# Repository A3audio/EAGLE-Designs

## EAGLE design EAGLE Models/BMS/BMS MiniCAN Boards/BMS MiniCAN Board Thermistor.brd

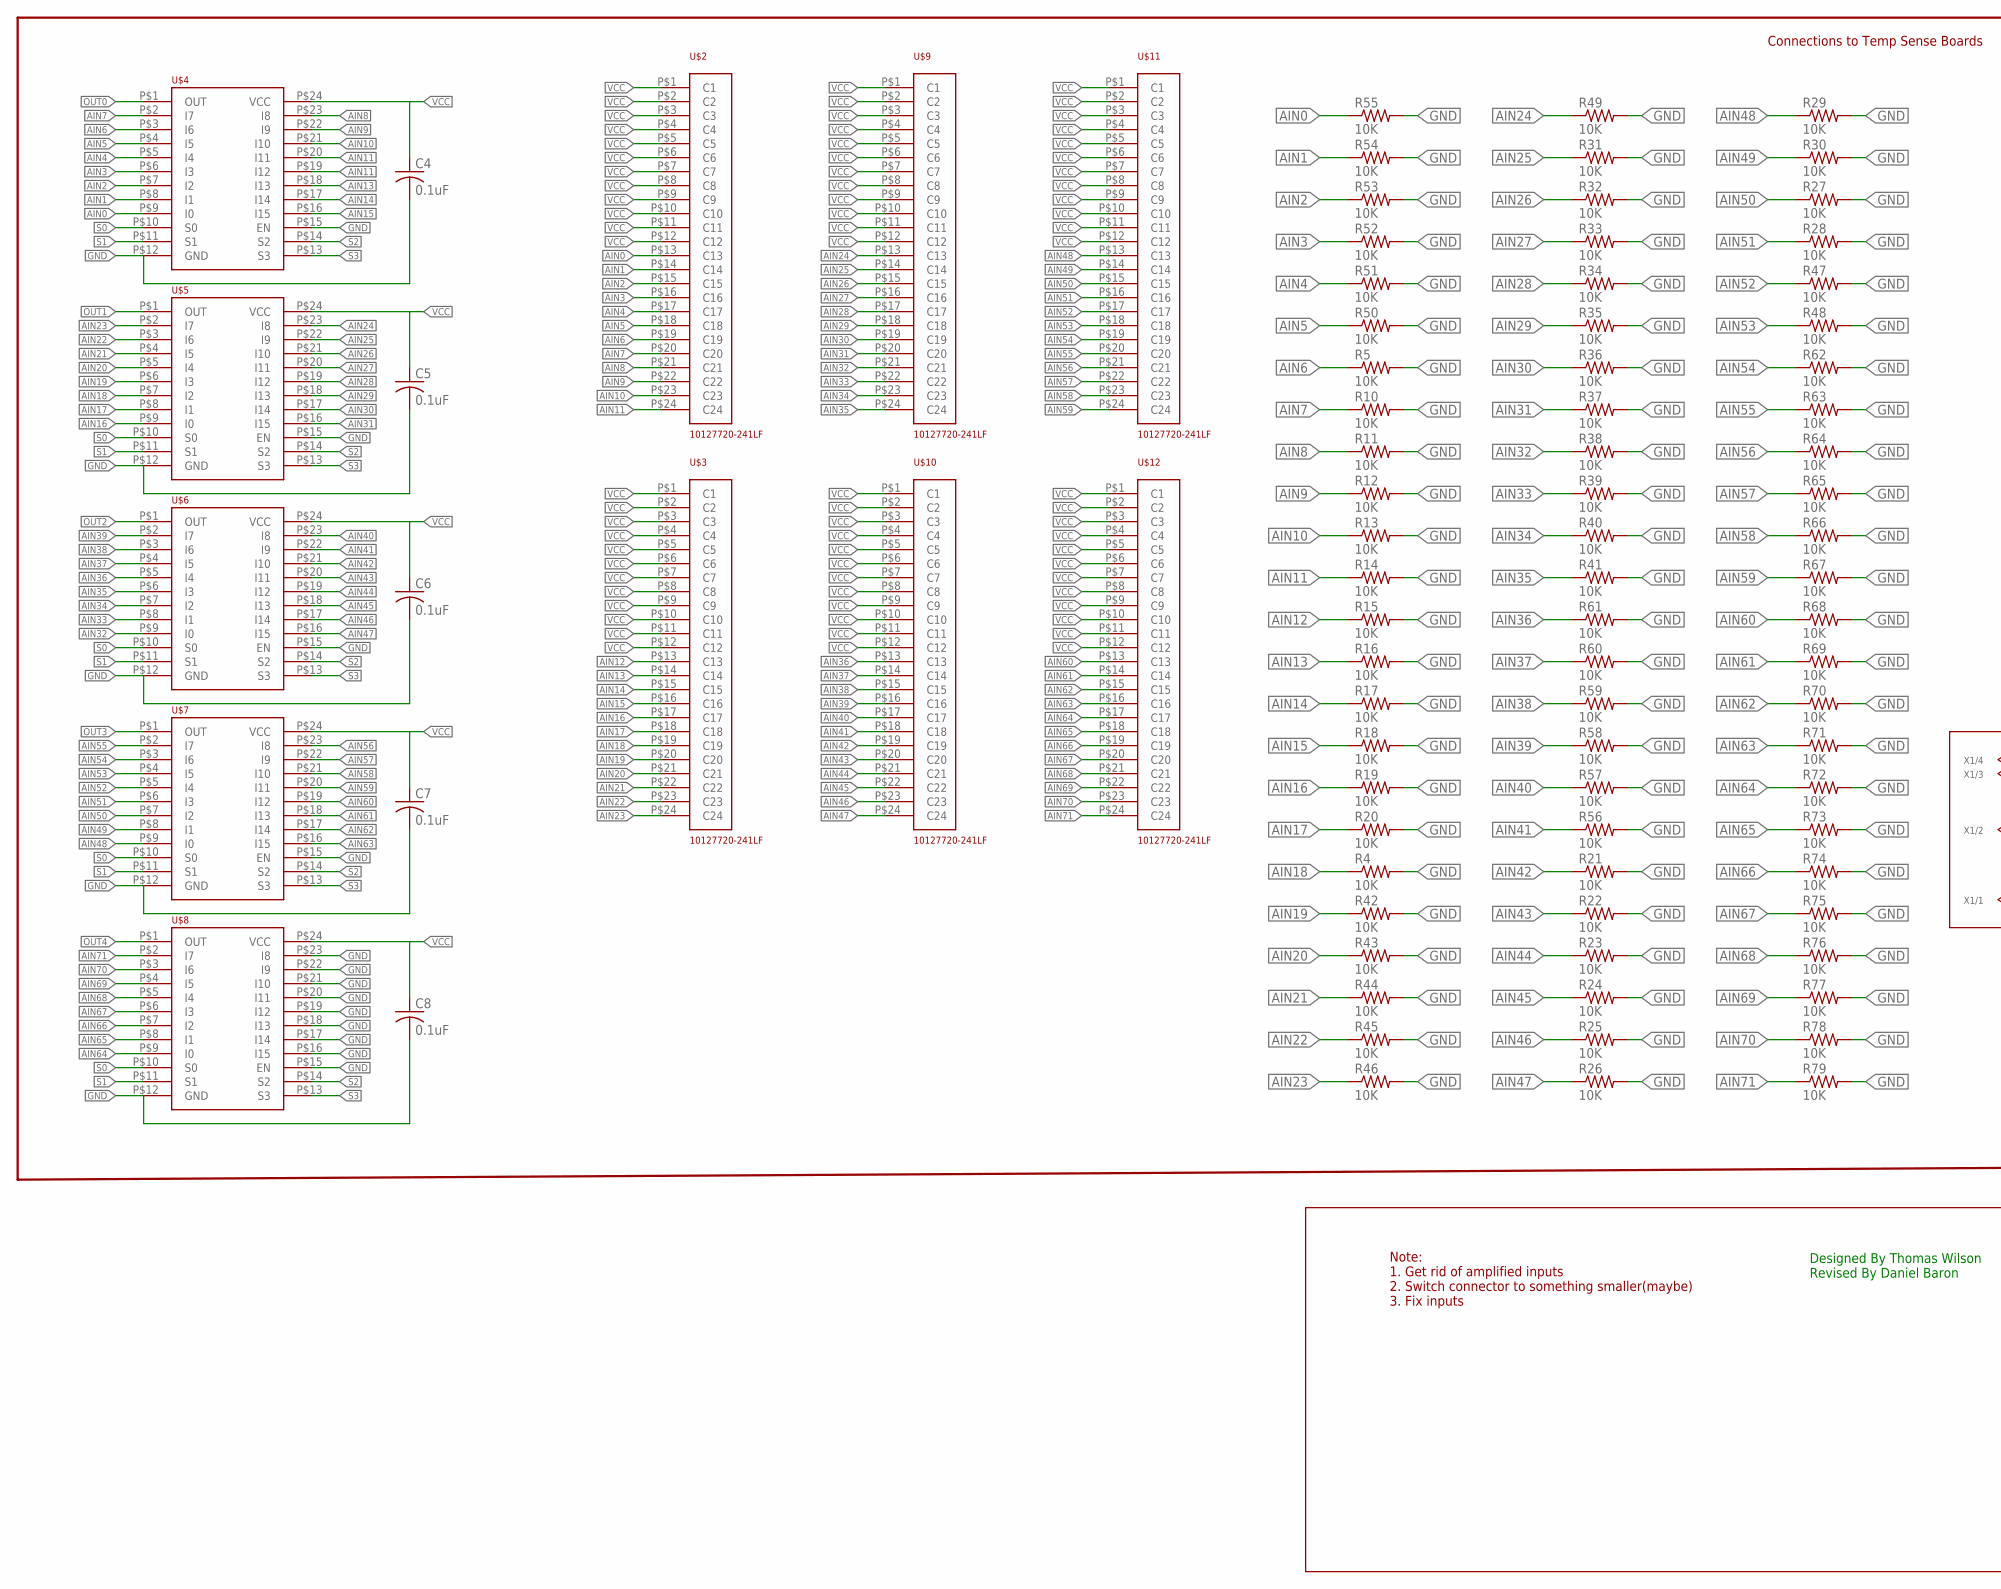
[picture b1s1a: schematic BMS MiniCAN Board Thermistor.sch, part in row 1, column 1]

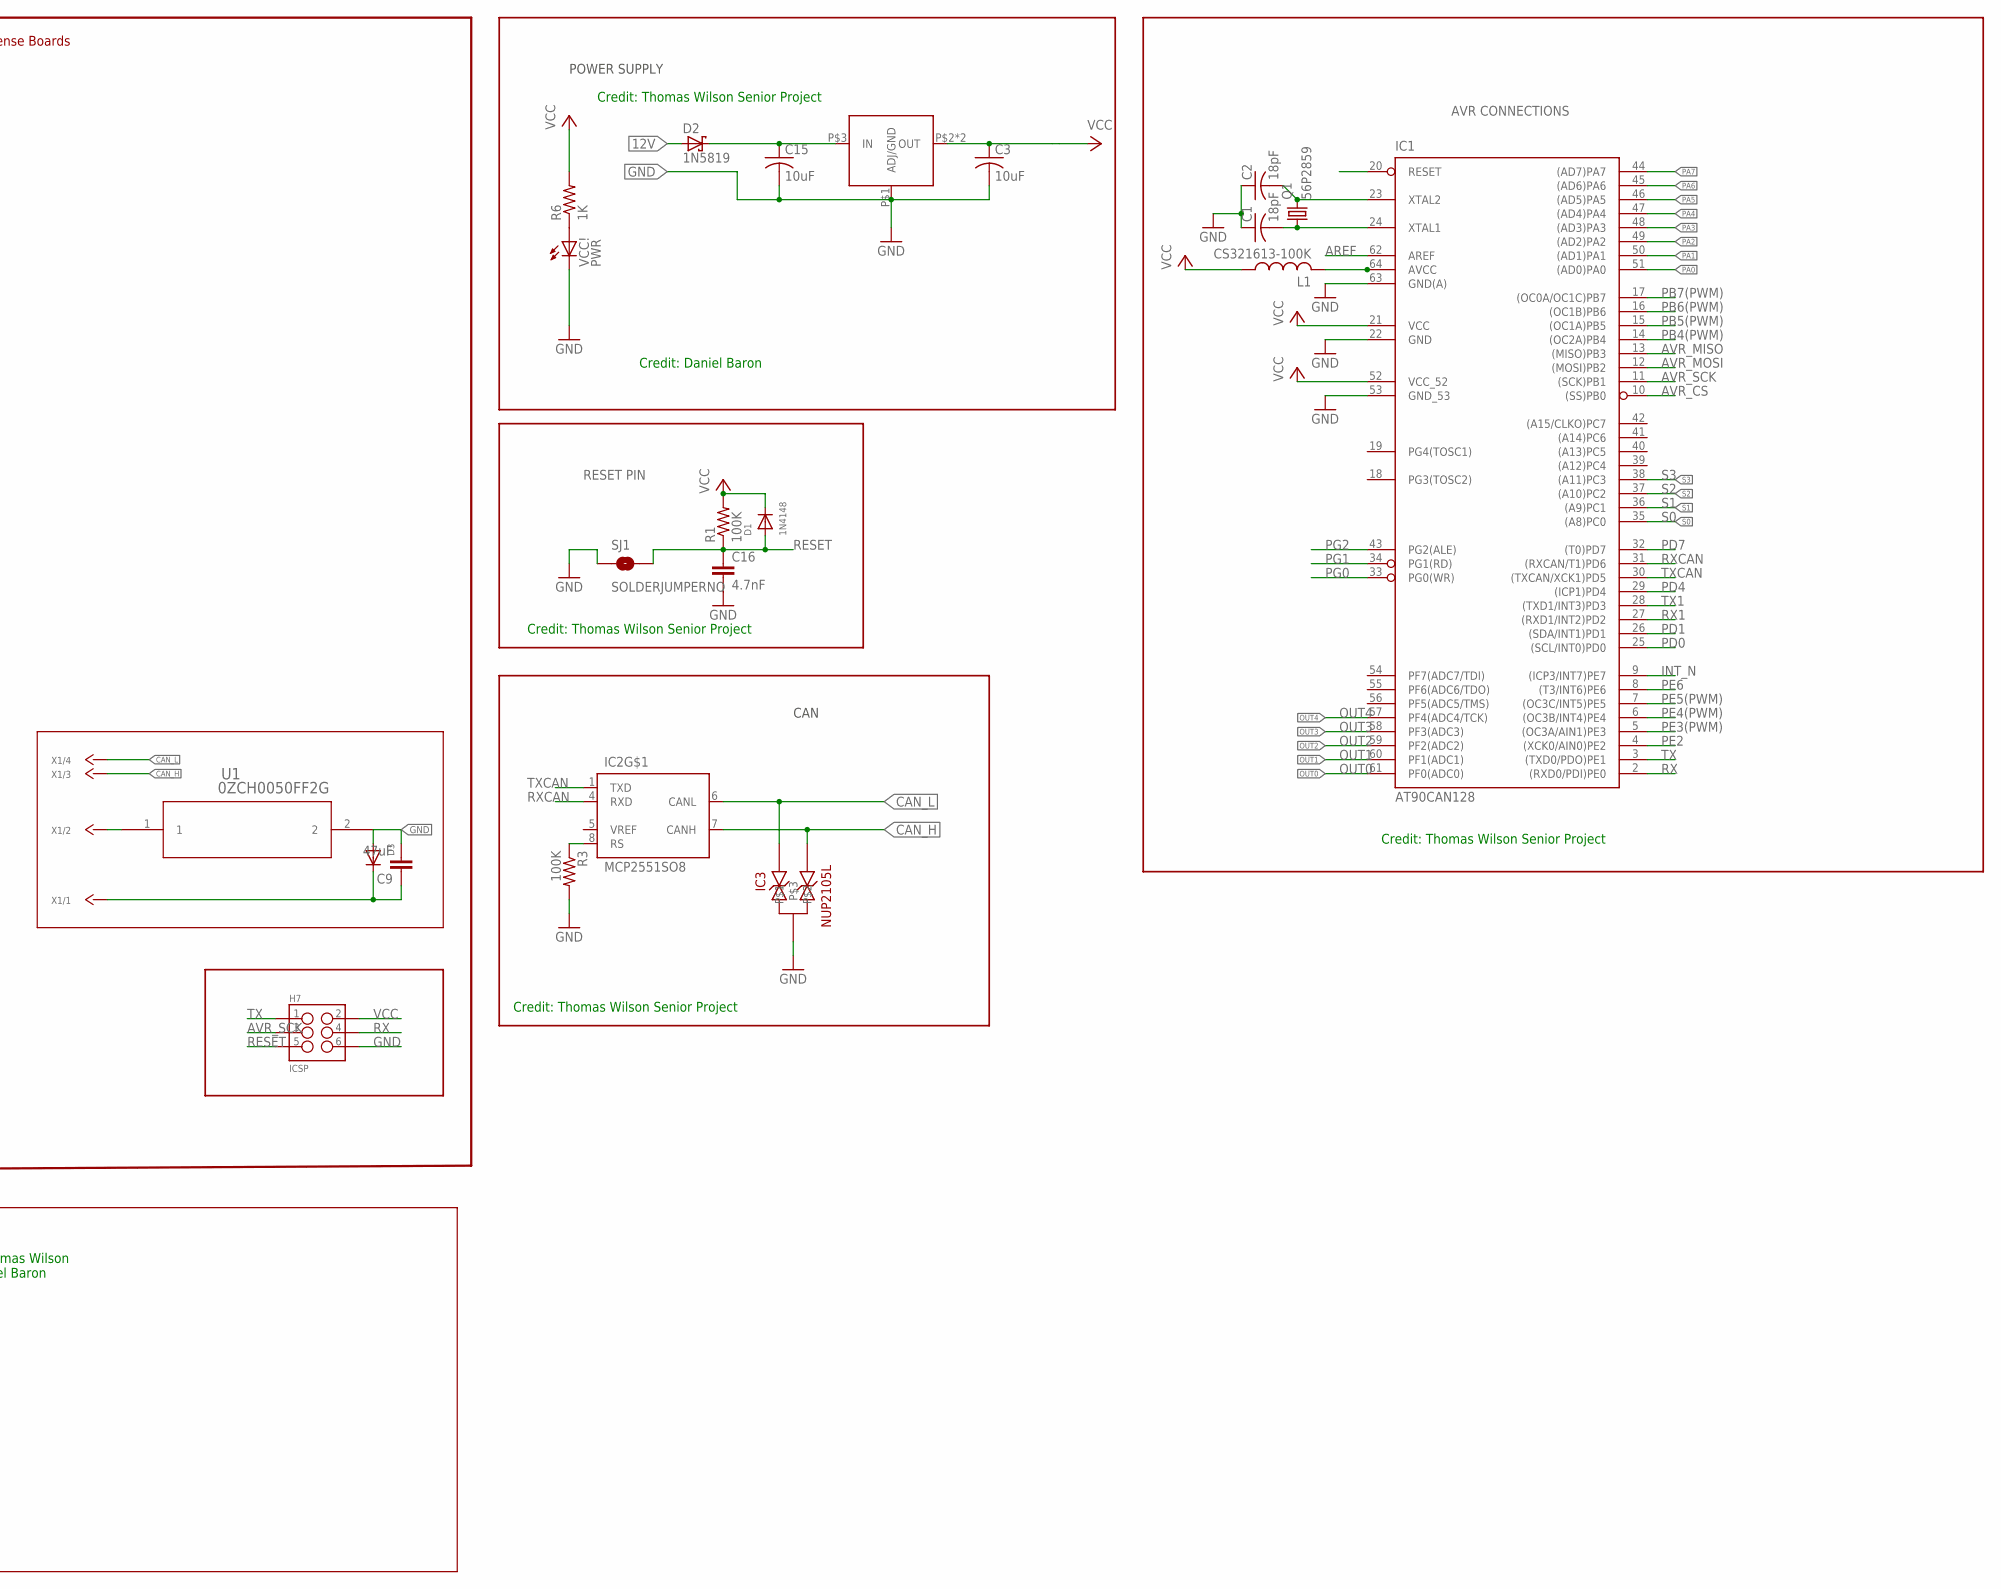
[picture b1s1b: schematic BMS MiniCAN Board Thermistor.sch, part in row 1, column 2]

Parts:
C1, C2: 18pF; C0805
C3, C15: 10uF; C0805
C4, C5, C6, C7, C8: 0.1uF; C0805
C9: 47uF; C0805
C16: 4.7nF; 0603-CAP
D1: 1N4148; SOD-123
D2: 1N5819; DO41-7.6
D3: DIODESOD-323F; SOD-323F
H7: ICSP; 2X3_SMD_FCI_54202-G30
IC1: AT90CAN128; TQFP64
IC2: MCP2551SO8; SO08
IC3: NUP2105L; SOT-23
L1: CS321613-100K; L3216C
Q1: 56P2859; HC49UP
R1, R3: 100K; R0805
R4, R5, R10, R11, R12, R13, R14, R15, R16, R17, R18, R19, R20, R21, R22, R23, R24, R25, R26, R27, R28, R29, R30, R31, R32, R33, R34, R35, R36, R37, R38, R39, R40, R41, R42, R43, R44, R45, R46, R47, R48, R49, R50, R51, R52, R53, R54, R55, R56, R57, R58, R59, R60, R61, R62, R63, R64, R65, R66, R67, R68, R69, R70, R71, R72, R73, R74, R75, R76, R77, R78, R79: 10K; R0603
R6: 1K; R0805
SJ1: SOLDERJUMPERNO; SJ_2S-NO
U1: 0ZCH0050FF2G; 0ZCH
U$1: LM117MPX-5.0; SOT223-4
U$2, U$3, U$9, U$10, U$11, U$12: 10127720-241LF
U$4, U$5, U$6, U$7, U$8: CD74HC4067; 24-SOIC
VCC!: PWR; CHIPLED_0805
X1: 4_PIN_CONN; 4_PIN_MOLEX

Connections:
12V: C9.1, D2.A, D3.C, X1.P$1
AIN0: R55.1, U$2.P$13 (C13), U$4.P$9 (I0)
AIN1: R54.1, U$2.P$14 (C14), U$4.P$8 (I1)
AIN2: R53.1, U$2.P$15 (C15), U$4.P$7 (I2)
AIN3: R52.1, U$2.P$16 (C16), U$4.P$6 (I3)
AIN4: R51.1, U$2.P$17 (C17), U$4.P$5 (I4)
AIN5: R50.1, U$2.P$18 (C18), U$4.P$4 (I5)
AIN6: R5.1, U$2.P$19 (C19), U$4.P$3 (I6)
AIN7: R10.1, U$2.P$20 (C20), U$4.P$2 (I7)
AIN8: R11.1, U$2.P$21 (C21), U$4.P$23 (I8)
AIN9: R12.1, U$2.P$22 (C22), U$4.P$22 (I9)
AIN10: R13.1, U$2.P$23 (C23), U$4.P$21 (I10)
AIN11: R14.1, U$2.P$24 (C24), U$4.P$19 (I12), U$4.P$20 (I11)
AIN12: R15.1, U$3.P$13 (C13)
AIN13: R16.1, U$3.P$14 (C14), U$4.P$18 (I13)
AIN14: R17.1, U$3.P$15 (C15), U$4.P$17 (I14)
AIN15: R18.1, U$3.P$16 (C16), U$4.P$16 (I15)
AIN16: R19.1, U$3.P$17 (C17), U$5.P$9 (I0)
AIN17: R20.1, U$3.P$18 (C18), U$5.P$8 (I1)
AIN18: R4.1, U$3.P$19 (C19), U$5.P$7 (I2)
AIN19: R42.1, U$3.P$20 (C20), U$5.P$6 (I3)
AIN20: R43.1, U$3.P$21 (C21), U$5.P$5 (I4)
AIN21: R44.1, U$3.P$22 (C22), U$5.P$4 (I5)
AIN22: R45.1, U$3.P$23 (C23), U$5.P$3 (I6)
AIN23: R46.1, U$3.P$24 (C24), U$5.P$2 (I7)
AIN24: R49.1, U$5.P$23 (I8), U$9.P$13 (C13)
AIN25: R31.1, U$5.P$22 (I9), U$9.P$14 (C14)
AIN26: R32.1, U$5.P$21 (I10), U$9.P$15 (C15)
AIN27: R33.1, U$5.P$20 (I11), U$9.P$16 (C16)
AIN28: R34.1, U$5.P$19 (I12), U$9.P$17 (C17)
AIN29: R35.1, U$5.P$18 (I13), U$9.P$18 (C18)
AIN30: R36.1, U$5.P$17 (I14), U$9.P$19 (C19)
AIN31: R37.1, U$5.P$16 (I15), U$9.P$20 (C20)
AIN32: R38.1, U$6.P$9 (I0), U$9.P$21 (C21)
AIN33: R39.1, U$6.P$8 (I1), U$9.P$22 (C22)
AIN34: R40.1, U$6.P$7 (I2), U$9.P$23 (C23)
AIN35: R41.1, U$6.P$6 (I3), U$9.P$24 (C24)
AIN36: R61.1, U$6.P$5 (I4), U$10.P$13 (C13)
AIN37: R60.1, U$6.P$4 (I5), U$10.P$14 (C14)
AIN38: R59.1, U$6.P$3 (I6), U$10.P$15 (C15)
AIN39: R58.1, U$6.P$2 (I7), U$10.P$16 (C16)
AIN40: R57.1, U$6.P$23 (I8), U$10.P$17 (C17)
AIN41: R56.1, U$6.P$22 (I9), U$10.P$18 (C18)
AIN42: R21.1, U$6.P$21 (I10), U$10.P$19 (C19)
AIN43: R22.1, U$6.P$20 (I11), U$10.P$20 (C20)
AIN44: R23.1, U$6.P$19 (I12), U$10.P$21 (C21)
AIN45: R24.1, U$6.P$18 (I13), U$10.P$22 (C22)
AIN46: R25.1, U$6.P$17 (I14), U$10.P$23 (C23)
AIN47: R26.1, U$6.P$16 (I15), U$10.P$24 (C24)
AIN48: R29.1, U$7.P$9 (I0), U$11.P$13 (C13)
AIN49: R30.1, U$7.P$8 (I1), U$11.P$14 (C14)
AIN50: R27.1, U$7.P$7 (I2), U$11.P$15 (C15)
AIN51: R28.1, U$7.P$6 (I3), U$11.P$16 (C16)
AIN52: R47.1, U$7.P$5 (I4), U$11.P$17 (C17)
AIN53: R48.1, U$7.P$4 (I5), U$11.P$18 (C18)
AIN54: R62.1, U$7.P$3 (I6), U$11.P$19 (C19)
AIN55: R63.1, U$7.P$2 (I7), U$11.P$20 (C20)
AIN56: R64.1, U$7.P$23 (I8), U$11.P$21 (C21)
AIN57: R65.1, U$7.P$22 (I9), U$11.P$22 (C22)
AIN58: R66.1, U$7.P$21 (I10), U$11.P$23 (C23)
AIN59: R67.1, U$7.P$20 (I11), U$11.P$24 (C24)
AIN60: R68.1, U$7.P$19 (I12), U$12.P$13 (C13)
AIN61: R69.1, U$7.P$18 (I13), U$12.P$14 (C14)
AIN62: R70.1, U$7.P$17 (I14), U$12.P$15 (C15)
AIN63: R71.1, U$7.P$16 (I15), U$12.P$16 (C16)
AIN64: R72.1, U$8.P$9 (I0), U$12.P$17 (C17)
AIN65: R73.1, U$8.P$8 (I1), U$12.P$18 (C18)
AIN66: R74.1, U$8.P$7 (I2), U$12.P$19 (C19)
AIN67: R75.1, U$8.P$6 (I3), U$12.P$20 (C20)
AIN68: R76.1, U$8.P$5 (I4), U$12.P$21 (C21)
AIN69: R77.1, U$8.P$4 (I5), U$12.P$22 (C22)
AIN70: R78.1, U$8.P$3 (I6), U$12.P$23 (C23)
AIN71: R79.1, U$8.P$2 (I7), U$12.P$24 (C24)
AREF: IC1.62 (AREF)
AVR_CS: IC1.10 ((SS)PB0)
AVR_MISO: IC1.13 ((MISO)PB3)
AVR_MOSI: IC1.12 ((MOSI)PB2)
AVR_SCK: H7.3, IC1.11 ((SCK)PB1)
CAN_H: IC2.7 (CANH), IC3.2, X1.P$3
CAN_L: IC2.6 (CANL), IC3.1, X1.P$4
GND: C1.1, C2.1, C3.2, C4.2, C5.2, C6.2, C7.2, C8.2, C9.2, C15.2, C16.2, D3.A, H7.6, IC1.22 (GND), IC1.53 (GND_53), IC1.63 (GND(A)), IC2.2 (GND), IC3.3, R3.2, R4.2, R5.2, R10.2, R11.2, R12.2, R13.2, R14.2, R15.2, R16.2, R17.2, R18.2, R19.2, R20.2, R21.2, R22.2, R23.2, R24.2, R25.2, R26.2, R27.2, R28.2, R29.2, R30.2, R31.2, R32.2, R33.2, R34.2, R35.2, R36.2, R37.2, R38.2, R39.2, R40.2, R41.2, R42.2, R43.2, R44.2, R45.2, R46.2, R47.2, R48.2, R49.2, R50.2, R51.2, R52.2, R53.2, R54.2, R55.2, R56.2, R57.2, R58.2, R59.2, R60.2, R61.2, R62.2, R63.2, R64.2, R65.2, R66.2, R67.2, R68.2, R69.2, R70.2, R71.2, R72.2, R73.2, R74.2, R75.2, R76.2, R77.2, R78.2, R79.2, SJ1.1, U1.2, U$1.P$1 (ADJ/GND), U$4.P$12 (GND), U$4.P$15 (EN), U$5.P$12 (GND), U$5.P$15 (EN), U$6.P$12 (GND), U$6.P$15 (EN), U$7.P$12 (GND), U$7.P$15 (EN), U$8.P$12 (GND), U$8.P$15 (EN), U$8.P$16 (I15), U$8.P$17 (I14), U$8.P$18 (I13), U$8.P$19 (I12), U$8.P$20 (I11), U$8.P$21 (I10), U$8.P$22 (I9), U$8.P$23 (I8), VCC!.C
INT_N: IC1.9 ((ICP3/INT7)PE7)
unnamed: C15.1, D2.C, U$1.P$3 (IN)
unnamed: U1.1, X1.P$2
unnamed: IC2.8 (RS), R3.1
unnamed: R6.1, VCC!.A
unnamed: C1.2, IC1.24 (XTAL1), Q1.1
unnamed: IC1.64 (AVCC), L1.2
OUT0: IC1.61 (PF0(ADC0)), U$4.P$1 (OUT)
OUT1: IC1.60 (PF1(ADC1)), U$5.P$1 (OUT)
OUT2: IC1.59 (PF2(ADC2)), U$6.P$1 (OUT)
OUT3: IC1.58 (PF3(ADC3)), U$7.P$1 (OUT)
OUT4: IC1.57 (PF4(ADC4/TCK)), U$8.P$1 (OUT)
PA0: IC1.51 ((AD0)PA0)
PA1: IC1.50 ((AD1)PA1)
PA2: IC1.49 ((AD2)PA2)
PA3: IC1.48 ((AD3)PA3)
PA4: IC1.47 ((AD4)PA4)
PA5: IC1.46 ((AD5)PA5)
PA6: IC1.45 ((AD6)PA6)
PA7: IC1.44 ((AD7)PA7)
PB4(PWM): IC1.14 ((OC2A)PB4)
PB5(PWM): IC1.15 ((OC1A)PB5)
PB6(PWM): IC1.16 ((OC1B)PB6)
PB7(PWM): IC1.17 ((OC0A/OC1C)PB7)
PD0: IC1.25 ((SCL/INT0)PD0)
PD1: IC1.26 ((SDA/INT1)PD1)
PD4: IC1.29 ((ICP1)PD4)
PD7: IC1.32 ((T0)PD7)
PE2: IC1.4 ((XCK0/AIN0)PE2)
PE3(PWM): IC1.5 ((OC3A/AIN1)PE3)
PE4(PWM): IC1.6 ((OC3B/INT4)PE4)
PE5(PWM): IC1.7 ((OC3C/INT5)PE5)
PE6: IC1.8 ((T3/INT6)PE6)
PG0: IC1.33 (PG0(WR))
PG1: IC1.34 (PG1(RD))
PG2: IC1.43 (PG2(ALE))
RESET: C16.1, D1.A, H7.5, IC1.20 (RESET), R1.1, SJ1.2
RX: H7.4, IC1.2 ((RXD0/PDI)PE0)
RX1: IC1.27 ((RXD1/INT2)PD2)
RXCAN: IC1.31 ((RXCAN/T1)PD6), IC2.4 (RXD)
S0: IC1.35 ((A8)PC0), U$4.P$10 (S0), U$5.P$10 (S0), U$6.P$10 (S0), U$7.P$10 (S0), U$8.P$10 (S0)
S1: IC1.36 ((A9)PC1), U$4.P$11 (S1), U$5.P$11 (S1), U$6.P$11 (S1), U$7.P$11 (S1), U$8.P$11 (S1)
S2: IC1.37 ((A10)PC2), U$4.P$14 (S2), U$5.P$14 (S2), U$6.P$14 (S2), U$7.P$14 (S2), U$8.P$14 (S2)
S3: IC1.38 ((A11)PC3), U$4.P$13 (S3), U$5.P$13 (S3), U$6.P$13 (S3), U$7.P$13 (S3), U$8.P$13 (S3)
TX: H7.1, IC1.3 ((TXD0/PDO)PE1)
TX1: IC1.28 ((TXD1/INT3)PD3)
TXCAN: IC1.30 ((TXCAN/XCK1)PD5), IC2.1 (TXD)
VCC: C3.1, C4.1, C5.1, C6.1, C7.1, C8.1, D1.C, H7.2, IC1.21 (VCC), IC1.52 (VCC_52), IC2.3 (VCC), L1.1, R1.2, R6.2, U$1.P$2 (OUT), U$1.P$4 (OUT), U$2.P$1 (C1), U$2.P$2 (C2), U$2.P$3 (C3), U$2.P$4 (C4), U$2.P$5 (C5), U$2.P$6 (C6), U$2.P$7 (C7), U$2.P$8 (C8), U$2.P$9 (C9), U$2.P$10 (C10), U$2.P$11 (C11), U$2.P$12 (C12), U$3.P$1 (C1), U$3.P$2 (C2), U$3.P$3 (C3), U$3.P$4 (C4), U$3.P$5 (C5), U$3.P$6 (C6), U$3.P$7 (C7), U$3.P$8 (C8), U$3.P$9 (C9), U$3.P$10 (C10), U$3.P$11 (C11), U$3.P$12 (C12), U$4.P$24 (VCC), U$9.P$1 (C1), U$9.P$2 (C2), U$9.P$3 (C3), U$9.P$4 (C4), U$9.P$5 (C5), U$9.P$6 (C6), U$9.P$7 (C7), U$9.P$8 (C8), U$9.P$9 (C9), U$9.P$10 (C10), U$9.P$11 (C11), U$9.P$12 (C12), U$10.P$1 (C1), U$10.P$2 (C2), U$10.P$3 (C3), U$10.P$4 (C4), U$10.P$5 (C5), U$10.P$6 (C6), U$10.P$7 (C7), U$10.P$8 (C8), U$10.P$9 (C9), U$10.P$10 (C10), U$10.P$11 (C11), U$10.P$12 (C12), U$11.P$1 (C1), U$11.P$2 (C2), U$11.P$3 (C3), U$11.P$4 (C4), U$11.P$5 (C5), U$11.P$6 (C6), U$11.P$7 (C7), U$11.P$8 (C8), U$11.P$9 (C9), U$11.P$10 (C10), U$11.P$11 (C11), U$11.P$12 (C12), U$12.P$1 (C1), U$12.P$2 (C2), U$12.P$3 (C3), U$12.P$4 (C4), U$12.P$5 (C5), U$12.P$6 (C6), U$12.P$7 (C7), U$12.P$8 (C8), U$12.P$9 (C9), U$12.P$10 (C10), U$12.P$11 (C11), U$12.P$12 (C12)
XTAL1: C2.2, IC1.23 (XTAL2), Q1.2

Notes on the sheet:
POWER SUPPLY
CAN
RESET PIN
AVR CONNECTIONS
Credit: Thomas Wilson Senior Project
Designed By Thomas Wilson Revised By Daniel Baron
Credit: Daniel Baron
Note: 1. Get rid of amplified inputs 2. Switch connector to something smaller(maybe) 3. Fix inputs
Connections to Temp Sense Boards

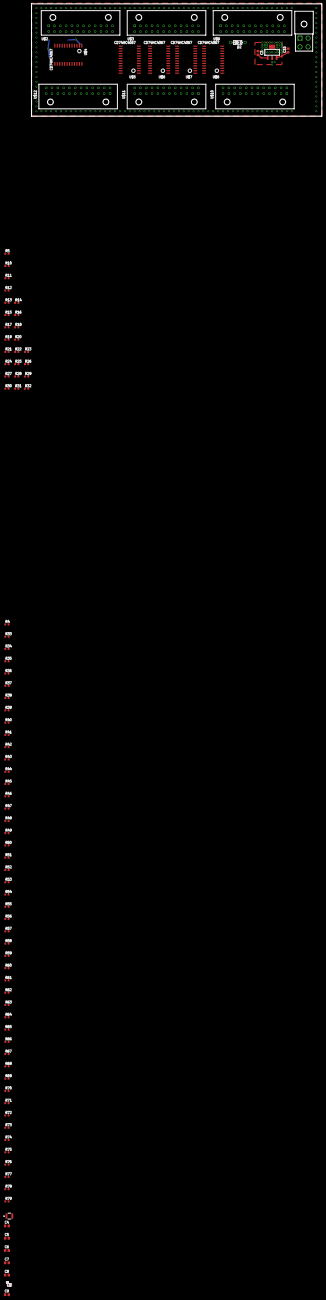
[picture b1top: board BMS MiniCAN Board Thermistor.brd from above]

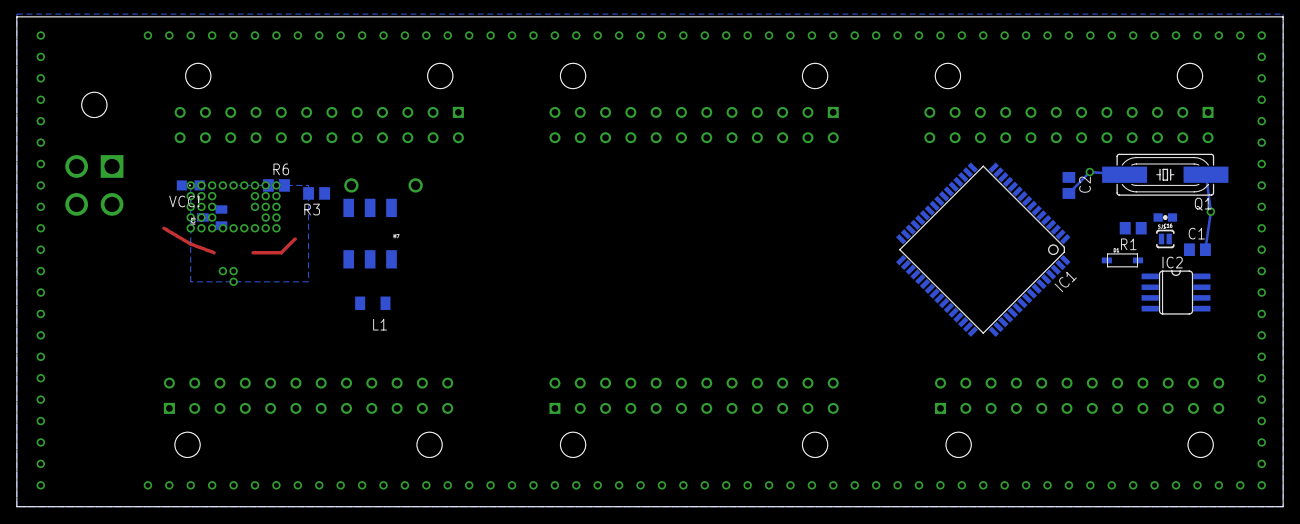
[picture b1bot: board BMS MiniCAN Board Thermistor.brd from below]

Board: 2 copper layers, 150.2 x 58.1 mm, 111 parts (15 on the bottom side), 99 nets.

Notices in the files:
parts and their libraries:
SparkFun-Capacitors: Licensing: CC v3.0 Share-Alike You are welcome to use this library for commercial purposes.
COPYRIGHT: Copyright (C) 2016 Accelerated Designs. All rights reserved
